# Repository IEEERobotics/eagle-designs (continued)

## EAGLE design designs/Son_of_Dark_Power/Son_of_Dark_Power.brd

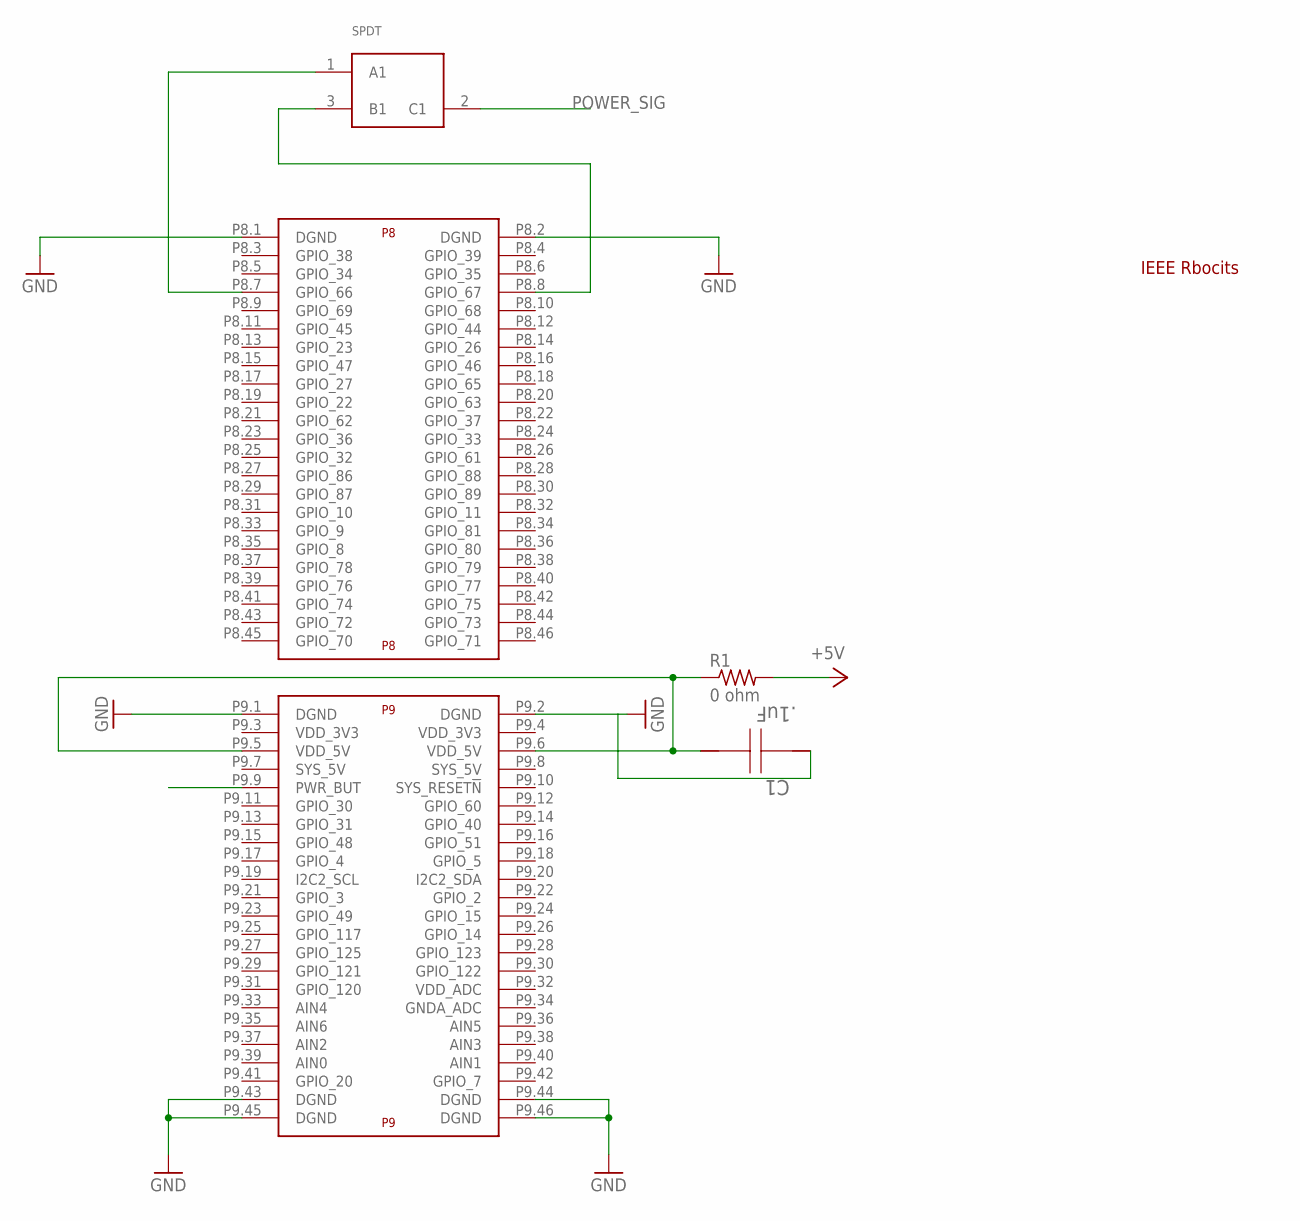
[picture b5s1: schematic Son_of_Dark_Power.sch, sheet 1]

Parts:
C1: .1uF; 1206
R1: 0 ohm; R1206
SPDT: SPDT_SWITCH; SPDT
U$1: BEAGLE_BONE_BLACK_CAPE
U$5: LOGO-IEEE; LOGO

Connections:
+5V: R1.2; also elsewhere on the board
BB_PWR_SW: U$1.P9.9 (PWR_BUT); also elsewhere on the board
GND: C1.2, U$1.P8.1 (DGND), U$1.P8.2 (DGND), U$1.P9.1 (DGND), U$1.P9.2 (DGND), U$1.P9.43 (DGND), U$1.P9.44 (DGND), U$1.P9.45 (DGND), U$1.P9.46 (DGND); also elsewhere on the board
unnamed: C1.1, R1.1, U$1.P9.5 (VDD_5V), U$1.P9.6 (VDD_5V)
unnamed: SPDT.1 (A1), U$1.P8.7 (GPIO_66)
unnamed: SPDT.3 (B1), U$1.P8.8 (GPIO_67)
POWER_SIG: SPDT.2 (C1); also elsewhere on the board

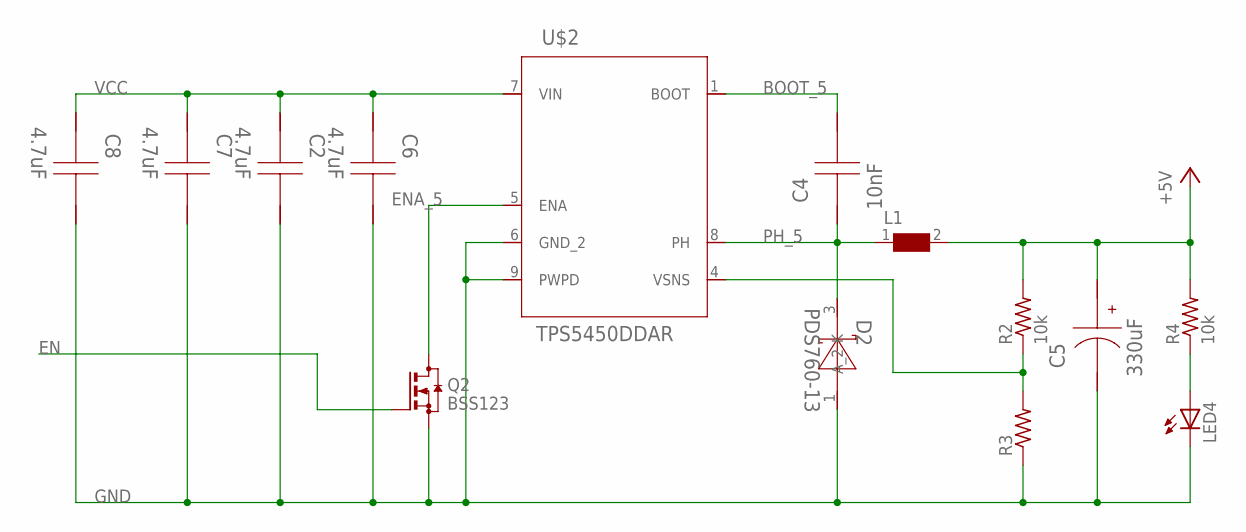
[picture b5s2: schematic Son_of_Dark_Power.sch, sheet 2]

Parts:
C2, C6, C7, C8: 4.7uF; 1206
C4: 10nF; 0805
C5: 330uF; SM_RADIAL_10AMM
D2: PDS760-13; POWERDI5
L1: WE-HCC-7443331000_1090; WE-HCC_1090
LED4: LEDSML1206; SML1206
Q2: BSS123; SOT23
R2, R4: 10k; R1206
R3: R-US_R1206; R1206
U$2: TPS5450DDAR; R-PDSO-G8

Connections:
+5V: C5.1 (+), L1.2, R2.2, R4.2; also elsewhere on the board
BOOT_5: C4.1, U$2.1 (BOOT)
EN: Q2.1 (G); also elsewhere on the board
ENA_5: Q2.3 (D), U$2.5 (ENA)
GND: C2.1, C5.2 (-), C6.1, C7.1, C8.1, D2.1 (A_2), LED4.C, Q2.2 (S), R3.1, U$2.6 (GND_2), U$2.9 (PWPD); also elsewhere on the board
unnamed: LED4.A, R4.1
PH_5: C4.2, D2.3 (K), L1.1, U$2.8 (PH)
VCC: C2.2, C6.2, C7.2, C8.2, U$2.7 (VIN); also elsewhere on the board
VSNS_5: R2.1, R3.2, U$2.4 (VSNS)

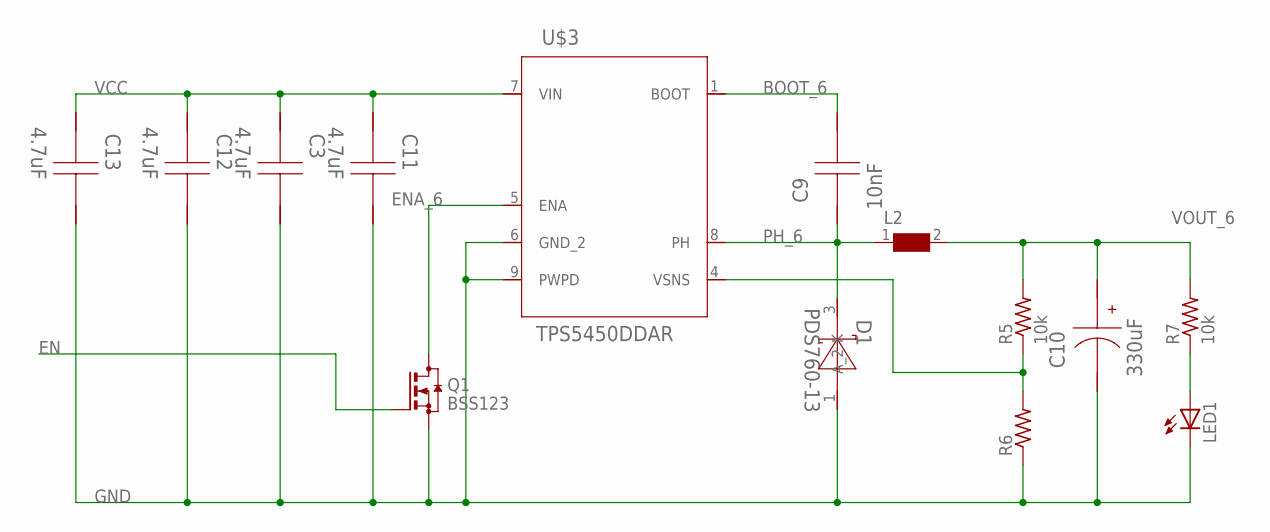
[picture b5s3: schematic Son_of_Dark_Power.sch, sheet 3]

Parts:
C3, C11, C12, C13: 4.7uF; 1206
C9: 10nF; 0805
C10: 330uF; SM_RADIAL_10AMM
D1: PDS760-13; POWERDI5
L2: WE-HCC-7443331000_1090; WE-HCC_1090
LED1: LEDSML1206; SML1206
Q1: BSS123; SOT23
R5, R7: 10k; R1206
R6: R-US_R1206; R1206
U$3: TPS5450DDAR; R-PDSO-G8

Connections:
BOOT_6: C9.1, U$3.1 (BOOT)
EN: Q1.1 (G); also elsewhere on the board
ENA_6: Q1.3 (D), U$3.5 (ENA)
GND: C3.1, C10.2 (-), C11.1, C12.1, C13.1, D1.1 (A_2), LED1.C, Q1.2 (S), R6.1, U$3.6 (GND_2), U$3.9 (PWPD); also elsewhere on the board
unnamed: LED1.A, R7.1
PH_6: C9.2, D1.3 (K), L2.1, U$3.8 (PH)
VCC: C3.2, C11.2, C12.2, C13.2, U$3.7 (VIN); also elsewhere on the board
VOUT_6: C10.1 (+), L2.2, R5.2, R7.2; also elsewhere on the board
VSNS_6: R5.1, R6.2, U$3.4 (VSNS)

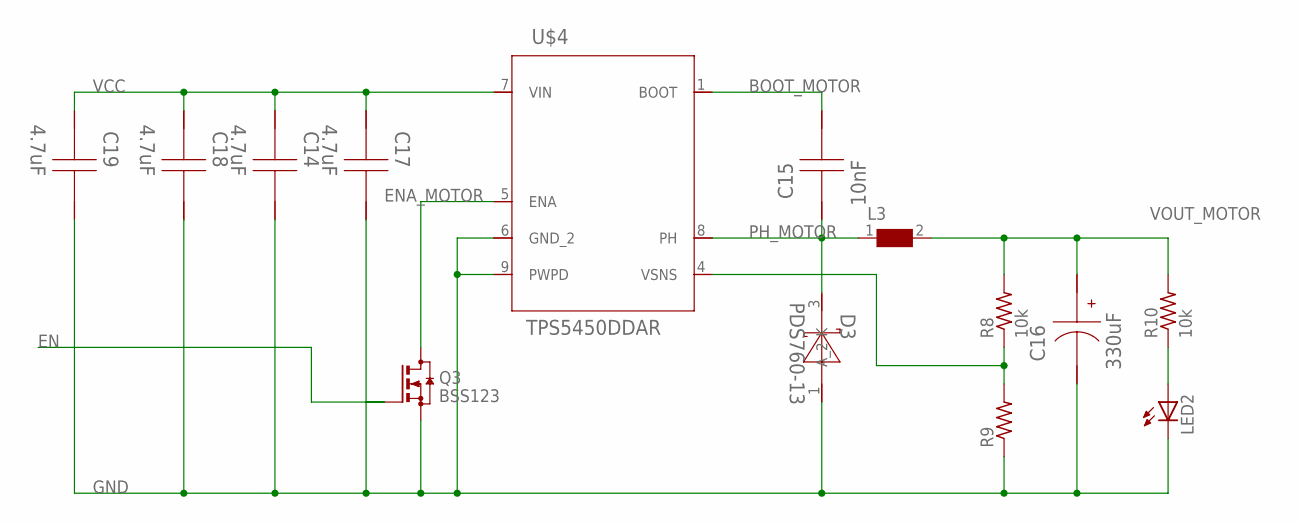
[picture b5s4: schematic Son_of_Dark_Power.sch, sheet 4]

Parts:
C14, C17, C18, C19: 4.7uF; 1206
C15: 10nF; 0805
C16: 330uF; SM_RADIAL_10AMM
D3: PDS760-13; POWERDI5
L3: WE-HCC-7443331000_1090; WE-HCC_1090
LED2: LEDSML1206; SML1206
Q3: BSS123; SOT23
R8, R10: 10k; R1206
R9: R-US_R1206; R1206
U$4: TPS5450DDAR; R-PDSO-G8

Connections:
BOOT_MOTOR: C15.1, U$4.1 (BOOT)
EN: Q3.1 (G); also elsewhere on the board
ENA_MOTOR: Q3.3 (D), U$4.5 (ENA)
GND: C14.1, C16.2 (-), C17.1, C18.1, C19.1, D3.1 (A_2), LED2.C, Q3.2 (S), R9.1, U$4.6 (GND_2), U$4.9 (PWPD); also elsewhere on the board
unnamed: LED2.A, R10.1
PH_MOTOR: C15.2, D3.3 (K), L3.1, U$4.8 (PH)
VCC: C14.2, C17.2, C18.2, C19.2, U$4.7 (VIN); also elsewhere on the board
VOUT_MOTOR: C16.1 (+), L3.2, R8.2, R10.2; also elsewhere on the board
VSNS1_MOTOR: R8.1, R9.2, U$4.4 (VSNS)

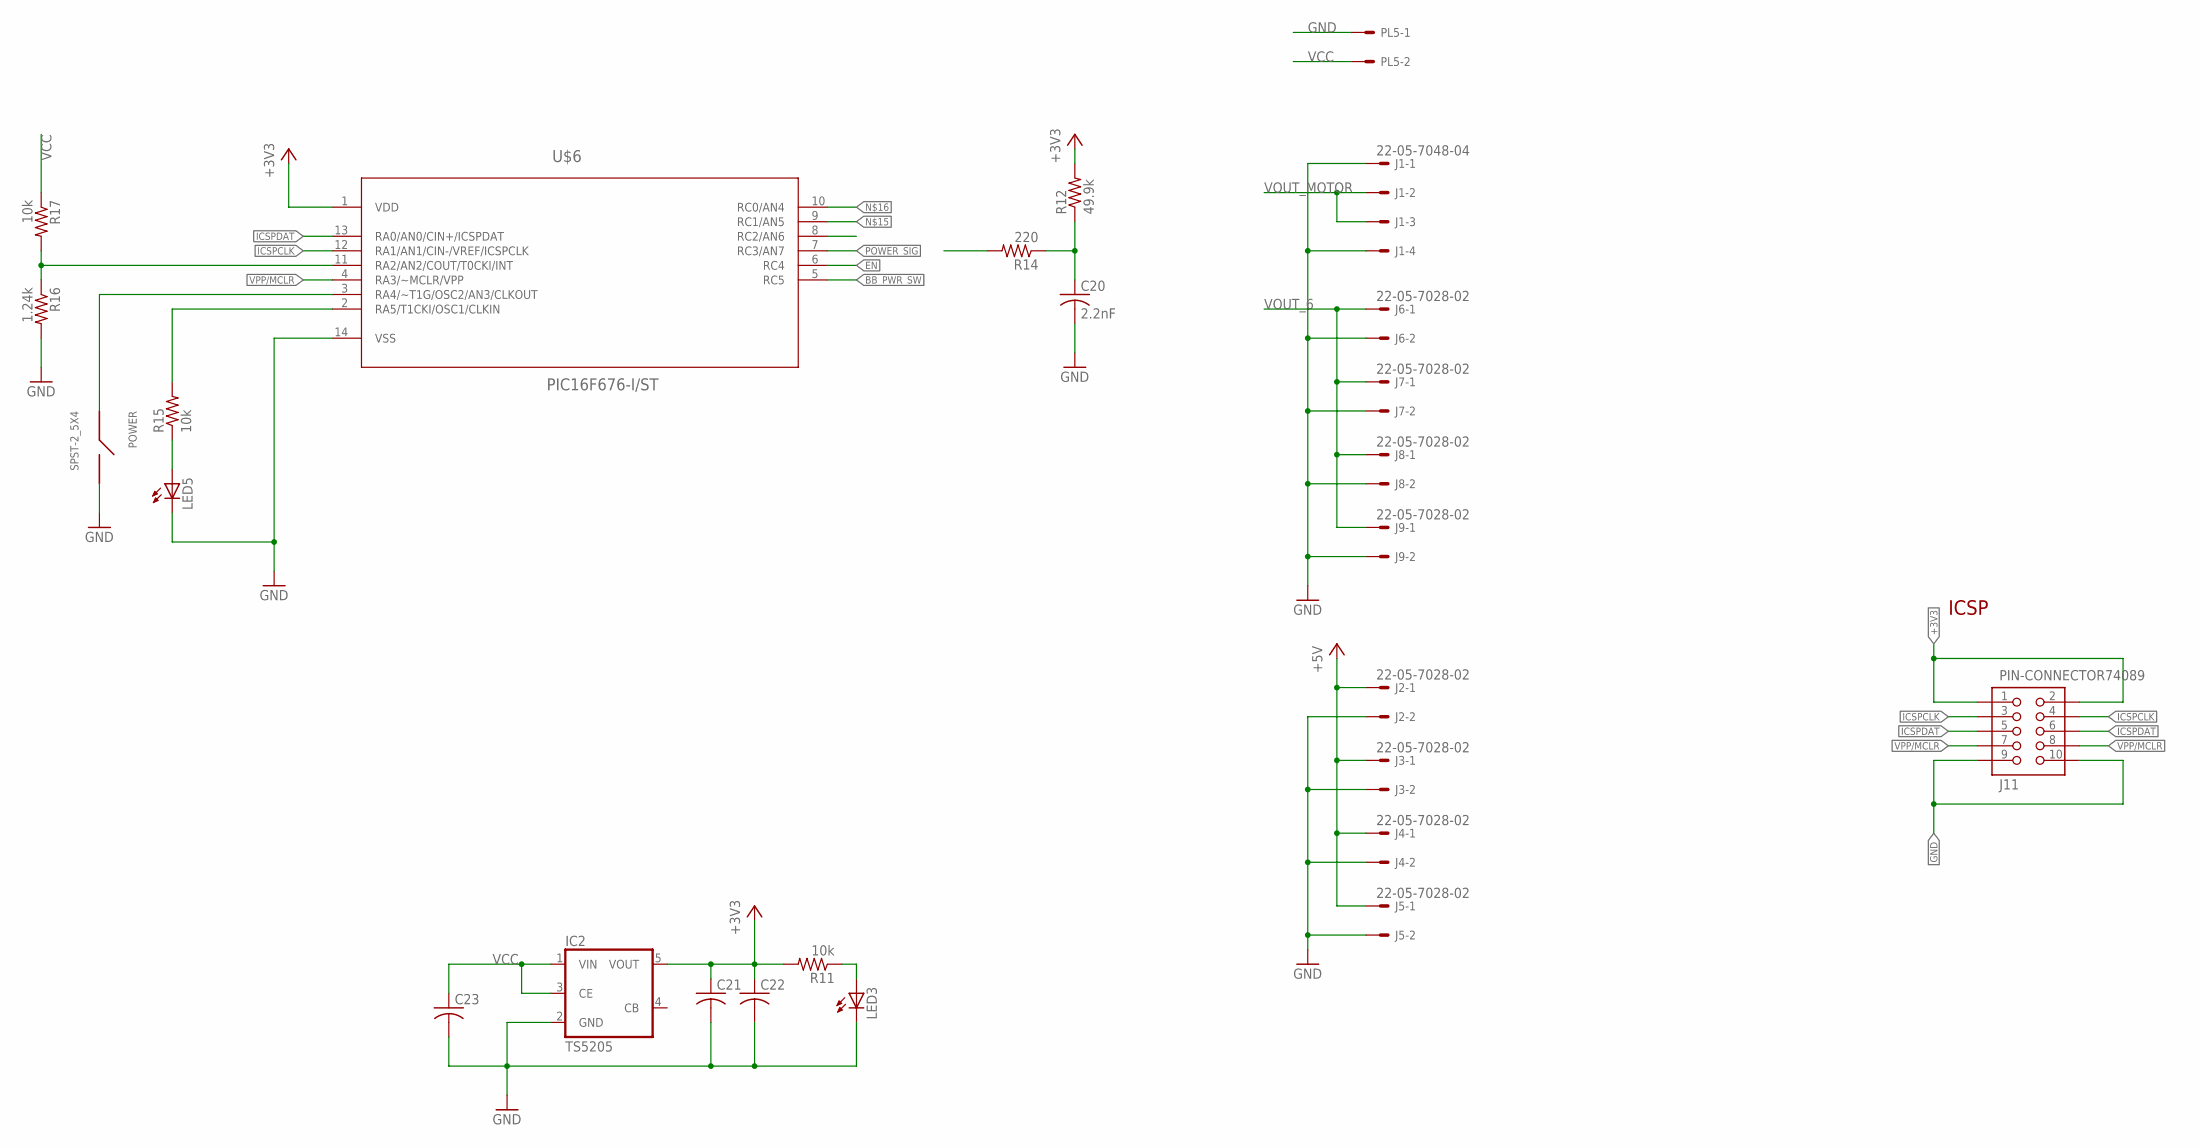
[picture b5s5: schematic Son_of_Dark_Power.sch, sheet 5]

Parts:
C20: 2.2nF; C0603
C21, C22, C23: C-USC0603; C0603
IC2: TS5205; SOT25
J1: 22-05-7048-04; 7395-04
J2, J3, J4, J5, J6, J7, J8, J9: 22-05-7028-02; 7395-02
J11: PIN-CONNECTOR74089; 10-PIN-SMD
LED3, LED5: LEDSML1206; SML1206
PL5: 555X-2H; 5569-2
POWER: SPST-2_5X4; SPST-TAC-4X2_5MM
R11, R15: 10k; R1206
R12: 49.9k; R0603
R14: 220; R0603
R16: 1.24k; R0603
R17: 10k; R0603
U$6: PIC16F676-I/ST; SOP65P640X120-14N

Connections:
+3V3: C21.1, C22.1, IC2.5 (VOUT), J11.1, J11.2, R11.2, R12.2, U$6.1 (VDD)
+5V: J2.1, J3.1, J4.1, J5.1; also elsewhere on the board
BB_PWR_SW: U$6.5 (RC5); also elsewhere on the board
EN: U$6.6 (RC4); also elsewhere on the board
GND: C20.2, C21.2, C22.2, C23.2, IC2.2 (GND), J1.1, J1.4, J2.2, J3.2, J4.2, J5.2, J6.2, J7.2, J8.2, J9.2, J11.9, J11.10, LED3.C, LED5.C, PL5.1, POWER.P$2, R16.2, U$6.14 (VSS); also elsewhere on the board
ICSPCLK: J11.3, J11.4, U$6.12 (RA1/AN1/CIN-/VREF/ICSPCLK)
ICSPDAT: J11.5, J11.6, U$6.13 (RA0/AN0/CIN+/ICSPDAT)
unnamed: C20.1, R12.1, R14.1
unnamed: LED3.A, R11.1
unnamed: R16.1, R17.2, U$6.11 (RA2/AN2/COUT/T0CKI/INT)
unnamed: R15.2, U$6.2 (RA5/T1CKI/OSC1/CLKIN)
unnamed: LED5.A, R15.1
unnamed: POWER.P$1, U$6.3 (RA4/~T1G/OSC2/AN3/CLKOUT)
POWER_SIG: U$6.7 (RC3/AN7); also elsewhere on the board
VCC: C23.1, IC2.1 (VIN), IC2.3 (CE), PL5.2, R17.1; also elsewhere on the board
VOUT_6: J6.1, J7.1, J8.1, J9.1; also elsewhere on the board
VOUT_MOTOR: J1.2, J1.3; also elsewhere on the board
VPP/MCLR: J11.7, J11.8, R14.2, U$6.4 (RA3/~MCLR/VPP)

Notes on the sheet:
ICSP

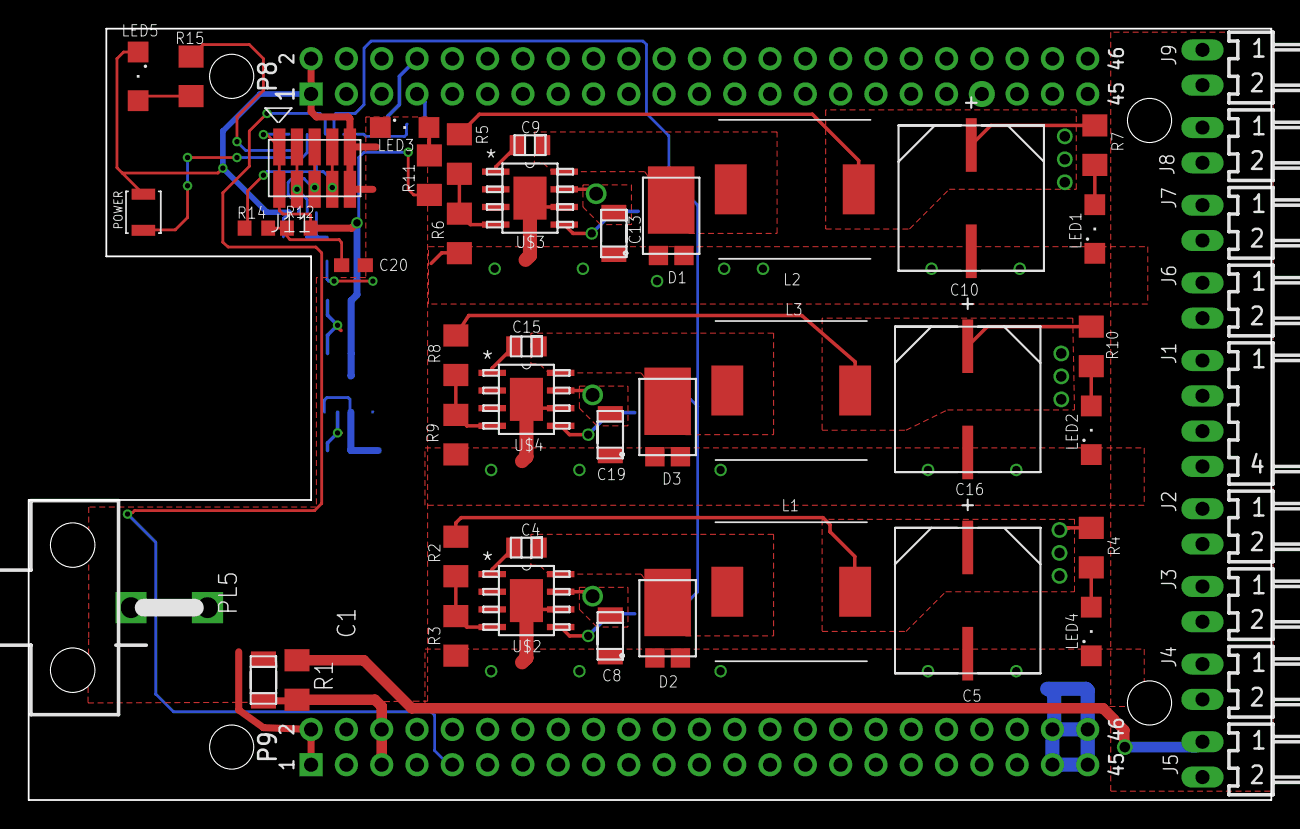
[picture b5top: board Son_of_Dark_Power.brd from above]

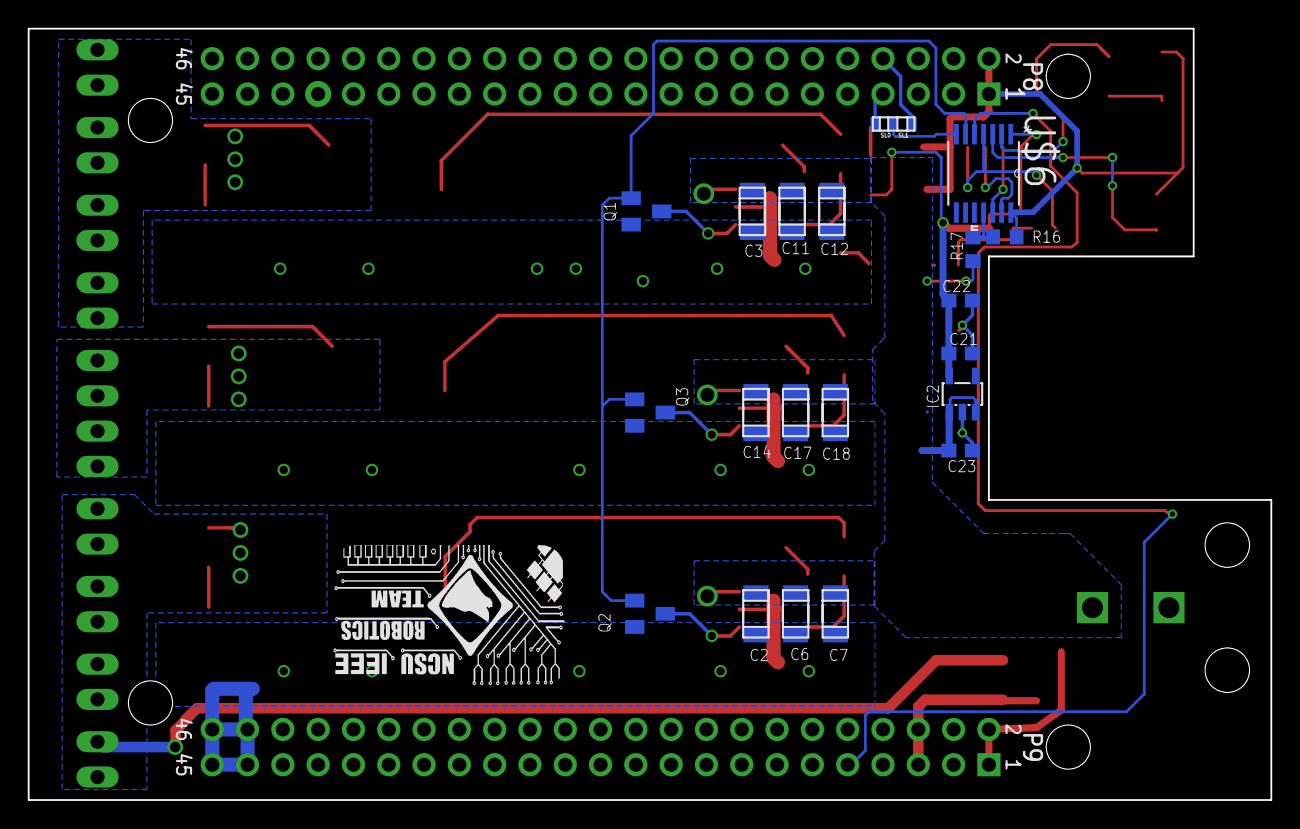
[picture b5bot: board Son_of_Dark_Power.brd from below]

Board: 2 copper layers, 89.4 x 55.5 mm, 73 parts (21 on the bottom side), 36 nets.
